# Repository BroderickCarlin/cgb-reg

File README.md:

# cgb-reg
CGB-REG chip replacement for Gameboy Color LCD drive circuitry

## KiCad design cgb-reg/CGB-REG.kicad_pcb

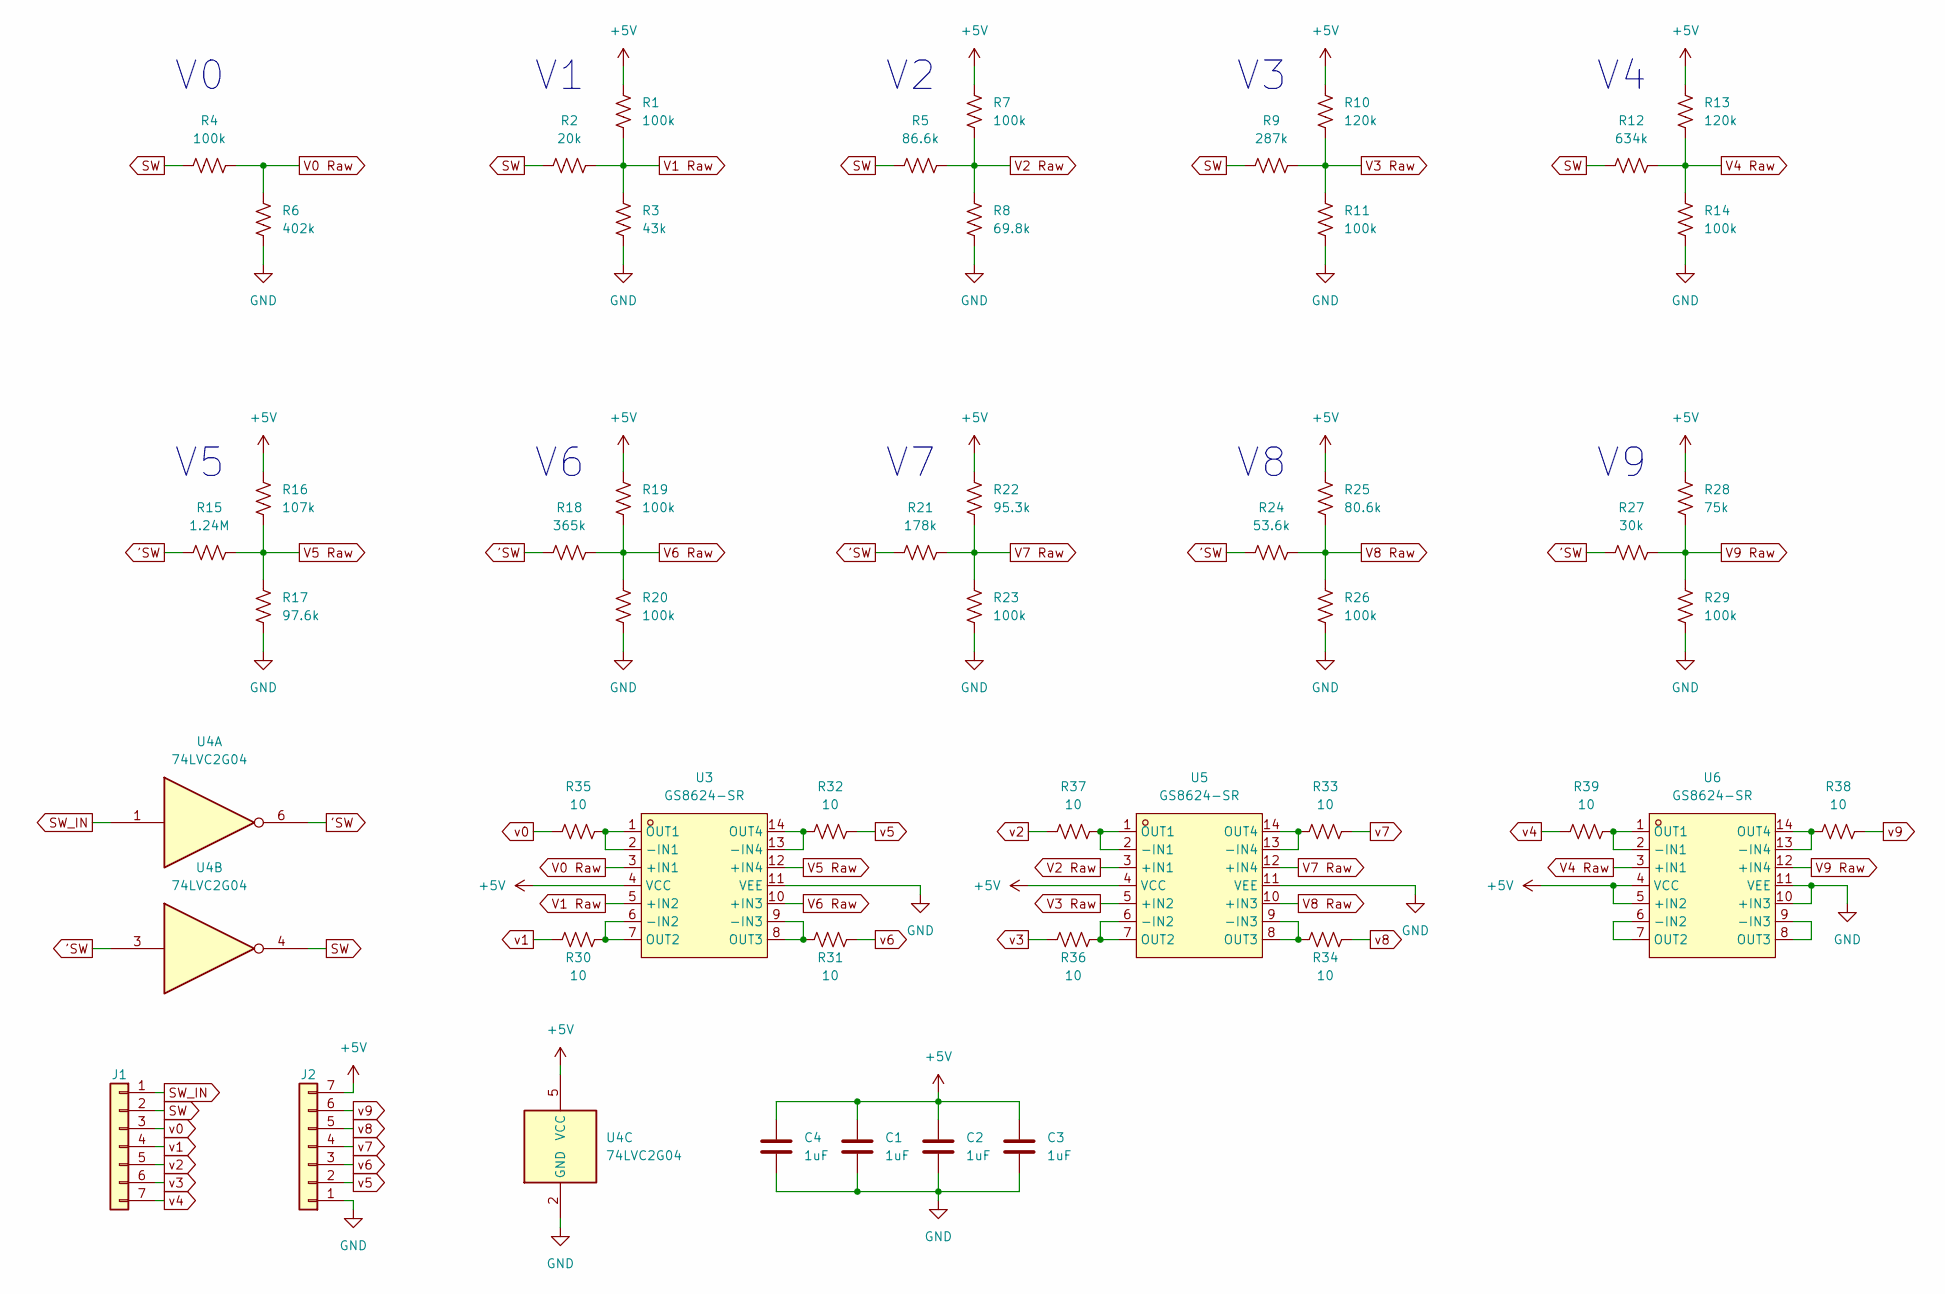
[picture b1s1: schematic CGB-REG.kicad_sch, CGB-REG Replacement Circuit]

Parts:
C1, C2, C3, C4: 1uF; C_0603_1608Metric; LCSC C89376
J1, J2: Conn_01x07; PinHeader_1x07_P2.54mm_Vertical
R1, R4, R7, R11, R14, R19, R20, R23, R26, R29: 100k; R_0603_1608Metric; LCSC C414506
R2: 20k; R_0603_1608Metric; LCSC C844340
R3: 43k; R_0603_1608Metric; LCSC C340523
R5: 86.6k; R_0603_1608Metric; LCSC C403381
R6: 402k; R_0603_1608Metric; LCSC C23048
R8: 69.8k; R_0603_1608Metric; LCSC C170663
R9: 287k; R_0603_1608Metric; LCSC C13174
R10, R13: 120k; R_0603_1608Metric; LCSC C325641
R12: 634k; R_0603_1608Metric; LCSC C321970
R15: 1.24M; R_0603_1608Metric; LCSC C367719
R16: 107k; R_0603_1608Metric; LCSC C103221
R17: 97.6k; R_0603_1608Metric; LCSC C507495
R18: 365k; R_0603_1608Metric; LCSC C367800
R21: 178k; R_0603_1608Metric; LCSC C103349
R22: 95.3k; R_0603_1608Metric; LCSC C912224
R24: 53.6k; R_0603_1608Metric; LCSC C103706
R25: 80.6k; R_0603_1608Metric; LCSC C2933260
R27: 30k; R_0603_1608Metric; LCSC C667692
R28: 75k; R_0603_1608Metric; LCSC C881187
R30, R31, R32, R33, R34, R35, R36, R37, R38, R39: 10; R_0603_1608Metric; LCSC C2791798
U3, U5, U6: GS8624-SR; SOIC-14_L8.6-W3.9-P1.27-LS6.0-BL; LCSC Part C605417
U4: 74LVC2G04; SOT-363_SC-70-6; LCSC C460538

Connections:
'SW: R15.2, R18.2, R21.2, R24.2, R27.2, U4.3, U4.6
+5V: C1.1, C2.1, C3.1, C4.1, J2.7, R1.1, R7.1, R10.1, R13.1, R16.1, R19.1, R22.1, R25.1, R28.1, U3.4 (VCC), U4.5 (VCC), U5.4 (VCC), U6.4 (VCC), U6.5 (+IN2)
GND: C1.2, C2.2, C3.2, C4.2, J2.1, R3.2, R6.2, R8.2, R11.2, R14.2, R17.2, R20.2, R23.2, R26.2, R29.2, U3.11 (VEE), U4.2 (GND), U5.11 (VEE), U6.10 (+IN3), U6.11 (VEE)
unnamed: R35.2, U3.1 (OUT1), U3.2 (-IN1)
unnamed: R30.2, U3.6 (-IN2), U3.7 (OUT2)
unnamed: R31.1, U3.8 (OUT3), U3.9 (-IN3)
unnamed: R32.1, U3.13 (-IN4), U3.14 (OUT4)
unnamed: R37.2, U5.1 (OUT1), U5.2 (-IN1)
unnamed: R36.2, U5.6 (-IN2), U5.7 (OUT2)
unnamed: R34.1, U5.8 (OUT3), U5.9 (-IN3)
unnamed: R33.1, U5.13 (-IN4), U5.14 (OUT4)
unnamed: R39.2, U6.1 (OUT1), U6.2 (-IN1)
unnamed: U6.6 (-IN2), U6.7 (OUT2)
unnamed: U6.8 (OUT3), U6.9 (-IN3)
unnamed: R38.2, U6.13 (-IN4), U6.14 (OUT4)
SW: J1.2, R2.2, R4.2, R5.2, R9.2, R12.2, U4.4
SW_IN: J1.1, U4.1
V0 Raw: R4.1, R6.1, U3.3 (+IN1)
V1 Raw: R1.2, R2.1, R3.1, U3.5 (+IN2)
V2 Raw: R5.1, R7.2, R8.1, U5.3 (+IN1)
V3 Raw: R9.1, R10.2, R11.1, U5.5 (+IN2)
V4 Raw: R12.1, R13.2, R14.1, U6.3 (+IN1)
V5 Raw: R15.1, R16.2, R17.1, U3.12 (+IN4)
V6 Raw: R18.1, R19.2, R20.1, U3.10 (+IN3)
V7 Raw: R21.1, R22.2, R23.1, U5.12 (+IN4)
V8 Raw: R24.1, R25.2, R26.1, U5.10 (+IN3)
V9 Raw: R27.1, R28.2, R29.1, U6.12 (+IN4)
v0: J1.3, R35.1
v1: J1.4, R30.1
v2: J1.5, R37.1
v3: J1.6, R36.1
v4: J1.7, R39.1
v5: J2.2, R32.2
v6: J2.3, R31.2
v7: J2.4, R33.2
v8: J2.5, R34.2
v9: J2.6, R38.1

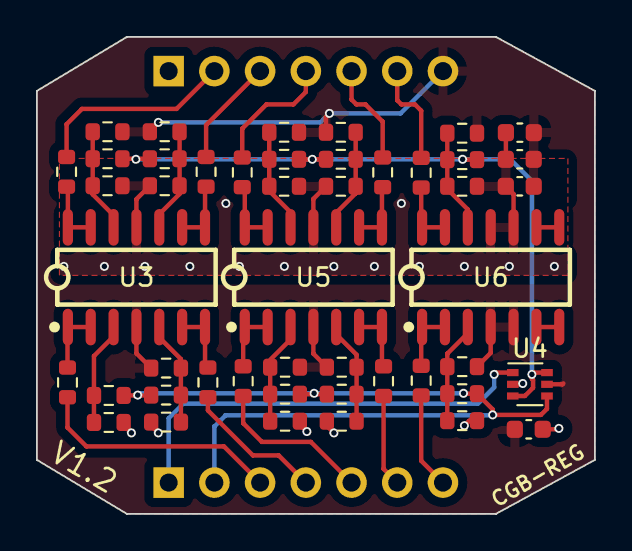
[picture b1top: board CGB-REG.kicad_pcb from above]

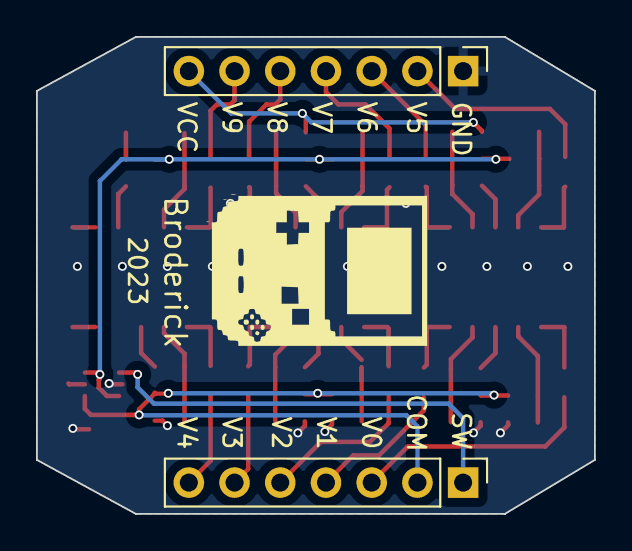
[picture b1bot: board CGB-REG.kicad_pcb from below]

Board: 2 copper layers, 31.0 x 26.5 mm, 49 parts (2 on the bottom side), 37 nets.

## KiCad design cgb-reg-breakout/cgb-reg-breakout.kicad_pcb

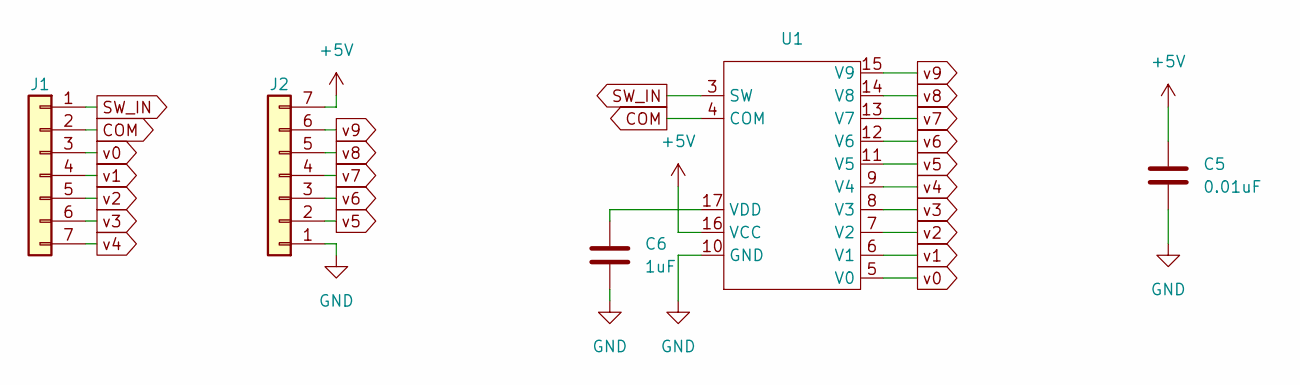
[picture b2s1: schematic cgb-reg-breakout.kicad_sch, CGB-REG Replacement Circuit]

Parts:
C5: 0.01uF; C_0603_1608Metric
C6: 1uF; C_0603_1608Metric; LCSC C89376
J1, J2: Conn_01x07; PinHeader_1x07_P2.54mm_Vertical
U1: CGB-REG

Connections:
+5V: C5.1, J2.7, U1.16 (VCC)
COM: J1.2, U1.4 (COM)
GND: C5.2, C6.2, J2.1, U1.10 (GND)
unnamed: C6.1, U1.17 (VDD)
SW_IN: J1.1, U1.3 (SW)
v0: J1.3, U1.5 (V0)
v1: J1.4, U1.6 (V1)
v2: J1.5, U1.7 (V2)
v3: J1.6, U1.8 (V3)
v4: J1.7, U1.9 (V4)
v5: J2.2, U1.11 (V5)
v6: J2.3, U1.12 (V6)
v7: J2.4, U1.13 (V7)
v8: J2.5, U1.14 (V8)
v9: J2.6, U1.15 (V9)

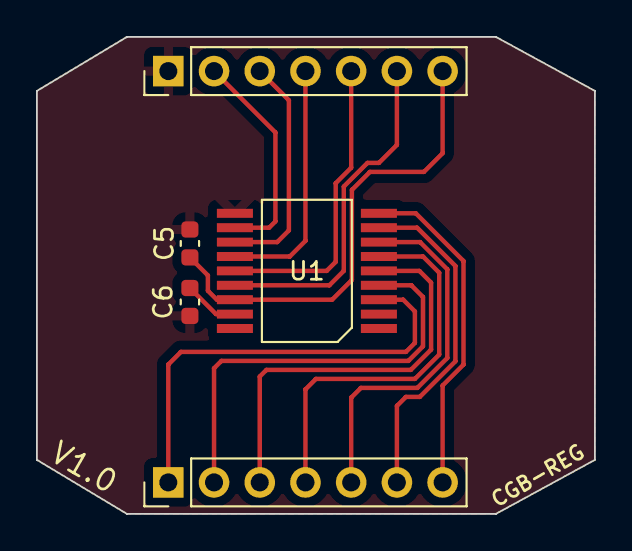
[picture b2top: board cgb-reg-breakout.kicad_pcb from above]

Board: 2 copper layers, 31.0 x 26.5 mm, 5 parts (0 on the bottom side), 15 nets.

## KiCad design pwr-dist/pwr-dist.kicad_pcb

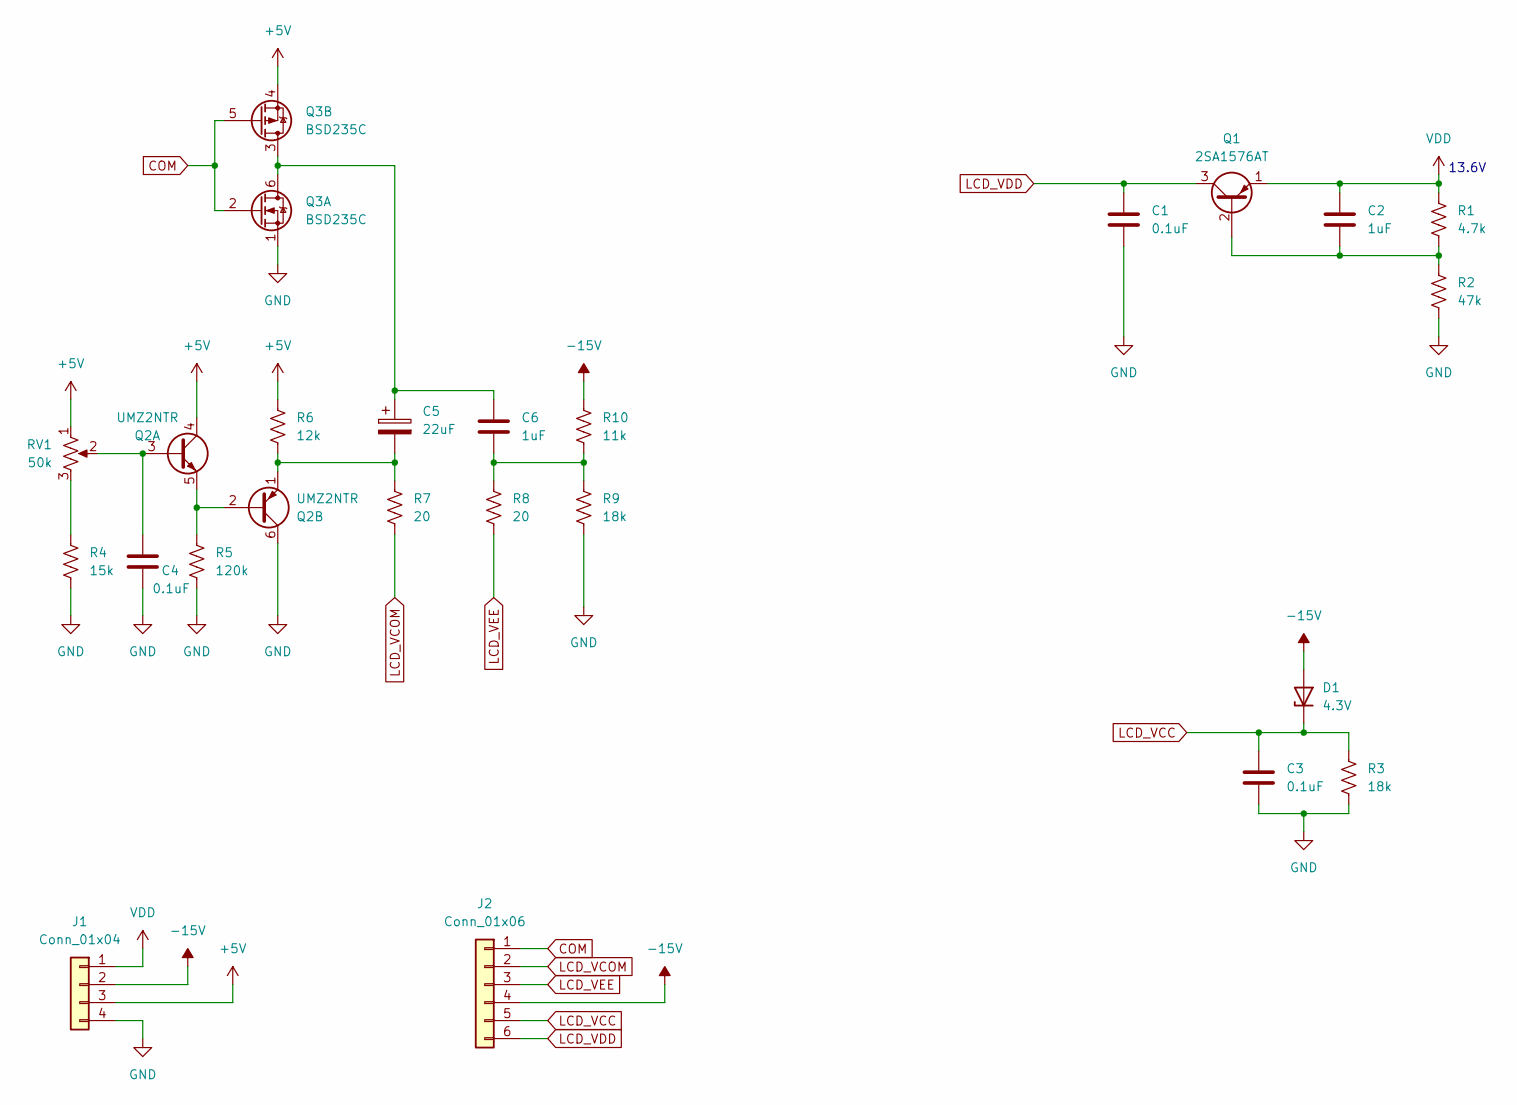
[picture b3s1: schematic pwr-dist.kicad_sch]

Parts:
C1, C3, C4: 0.1uF; R_0805_2012Metric_Pad1.20x1.40mm_HandSolder
C2, C6: 1uF; R_0805_2012Metric_Pad1.20x1.40mm_HandSolder
C5: 22uF; CP_Elec_4x5.3
D1: 4.3V; D_SOD-123
J1: Conn_01x04; PinHeader_1x04_P2.54mm_Vertical
J2: Conn_01x06; PinHeader_1x06_P2.54mm_Vertical
Q1: 2SA1576AT; SOT-323_SC-70_Handsoldering
Q2: UMZ2NTR; SOT-363_SC-70-6
Q3: BSD235C; SOT-666
R1: 4.7k; R_0805_2012Metric_Pad1.20x1.40mm_HandSolder
R2: 47k; R_0805_2012Metric_Pad1.20x1.40mm_HandSolder
R3, R9: 18k; R_0805_2012Metric_Pad1.20x1.40mm_HandSolder
R4: 15k; R_0805_2012Metric_Pad1.20x1.40mm_HandSolder
R5: 120k; R_0805_2012Metric_Pad1.20x1.40mm_HandSolder
R6: 12k; R_0805_2012Metric_Pad1.20x1.40mm_HandSolder
R7, R8: 20; R_0805_2012Metric_Pad1.20x1.40mm_HandSolder
R10: 11k; R_0805_2012Metric_Pad1.20x1.40mm_HandSolder
RV1: 50k; Potentiometer_Bourns_3314J_Vertical

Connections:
+5V: J1.3, Q2.4 (C1), Q3.4 (SP), R6.1, RV1.1
-15V: D1.2 (A), J1.2, J2.4, R10.1
COM: J2.1, Q3.2 (GN), Q3.5 (GP)
GND: C1.2, C3.2, C4.2, J1.4, Q2.6 (C2), Q3.1 (SN), R2.2, R3.2, R4.2, R5.2, R9.2
LCD_VCC: C3.1, D1.1 (K), J2.5, R3.1
LCD_VCOM: J2.2, R7.2
LCD_VDD: C1.1, J2.6, Q1.3 (C)
LCD_VEE: J2.3, R8.2
unnamed: C6.2, R8.1, R9.1, R10.2
unnamed: C2.2, Q1.2 (B), R1.2, R2.1
unnamed: C4.1, Q2.3 (B1), RV1.2
unnamed: Q2.2 (B2), Q2.5 (E1), R5.1
unnamed: C5.2, Q2.1 (E2), R6.2, R7.1
unnamed: C5.1, C6.1, Q3.3 (DP), Q3.6 (DN)
unnamed: R4.1, RV1.3
VDD: C2.1, J1.1, Q1.1 (E), R1.1

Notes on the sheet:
13.6V

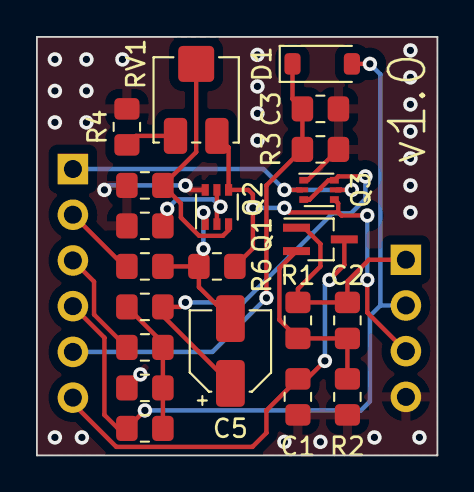
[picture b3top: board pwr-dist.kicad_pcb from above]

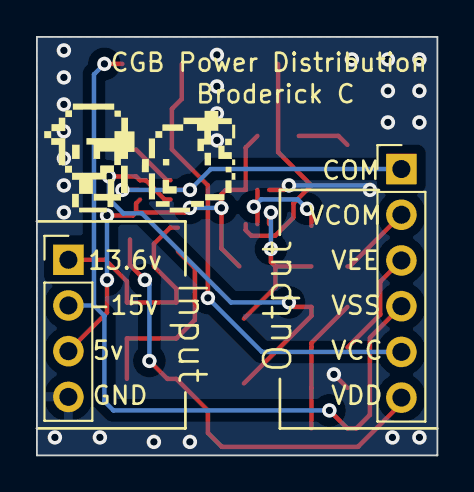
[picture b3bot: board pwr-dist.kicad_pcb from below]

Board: 2 copper layers, 22.2 x 23.2 mm, 23 parts (2 on the bottom side), 16 nets.

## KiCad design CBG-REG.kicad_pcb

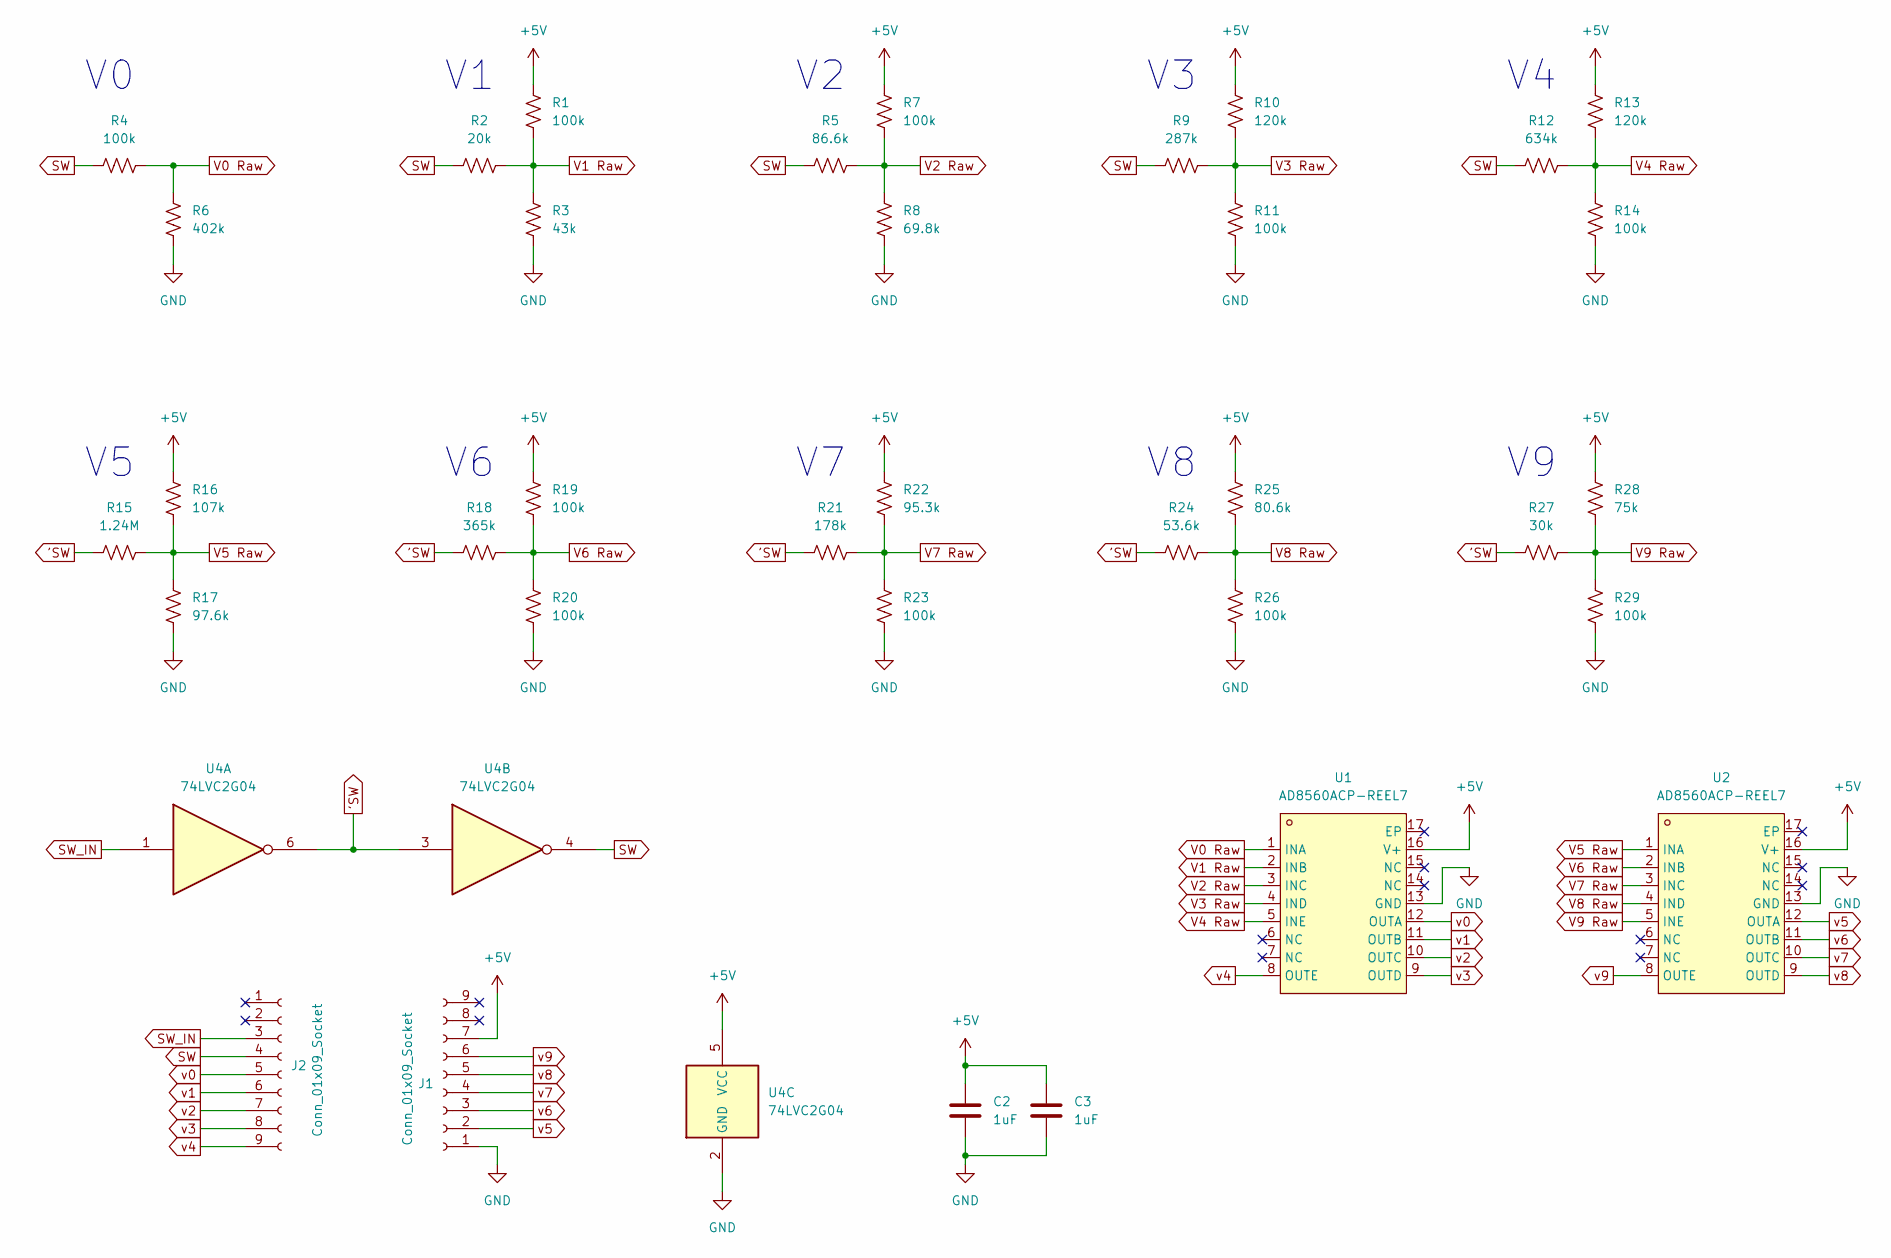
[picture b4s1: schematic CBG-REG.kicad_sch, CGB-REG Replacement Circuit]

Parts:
C2, C3: 1uF; C_0603_1608Metric; LCSC C89376
J1, J2: Conn_01x09_Socket; PinHeader_1x09_P2.00mm_Vertical
R1, R4, R7, R11, R14, R19, R20, R23, R26, R29: 100k; R_0603_1608Metric; LCSC C414506
R2: 20k; R_0603_1608Metric; LCSC C844340
R3: 43k; R_0603_1608Metric; LCSC C340523
R5: 86.6k; R_0603_1608Metric; LCSC C403381
R6: 402k; R_0603_1608Metric; LCSC C23048
R8: 69.8k; R_0603_1608Metric; LCSC C170663
R9: 287k; R_0603_1608Metric; LCSC C13174
R10, R13: 120k; R_0603_1608Metric; LCSC C325641
R12: 634k; R_0603_1608Metric; LCSC C321970
R15: 1.24M; R_0603_1608Metric; LCSC C367719
R16: 107k; R_0603_1608Metric; LCSC C103221
R17: 97.6k; R_0603_1608Metric; LCSC C507495
R18: 365k; R_0603_1608Metric; LCSC C367800
R21: 178k; R_0603_1608Metric; LCSC C103349
R22: 95.3k; R_0603_1608Metric; LCSC C912224
R24: 53.6k; R_0603_1608Metric; LCSC C103706
R25: 80.6k; R_0603_1608Metric; LCSC C2933260
R27: 30k; R_0603_1608Metric; LCSC C667692
R28: 75k; R_0603_1608Metric; LCSC C881187
U1, U2: AD8560ACP-REEL7; LFCSP-16_L4.0-W4.0-P0.65-TL-EP2.2; LCSC Part C4366758
U4: 74LVC2G04; SOT-23-6; LCSC C460538

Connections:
'SW: R15.2, R18.2, R21.2, R24.2, R27.2, U4.3, U4.6
+5V: C2.1, C3.1, J1.7, R1.1, R7.1, R10.1, R13.1, R16.1, R19.1, R22.1, R25.1, R28.1, U1.16 (V+), U2.16 (V+), U4.5 (VCC)
GND: C2.2, C3.2, J1.1, R3.2, R6.2, R8.2, R11.2, R14.2, R17.2, R20.2, R23.2, R26.2, R29.2, U1.13 (GND), U2.13 (GND), U4.2 (GND)
SW: J2.4, R2.2, R4.2, R5.2, R9.2, R12.2, U4.4
SW_IN: J2.3, U4.1
V0 Raw: R4.1, R6.1, U1.1 (INA)
V1 Raw: R1.2, R2.1, R3.1, U1.2 (INB)
V2 Raw: R5.1, R7.2, R8.1, U1.3 (INC)
V3 Raw: R9.1, R10.2, R11.1, U1.4 (IND)
V4 Raw: R12.1, R13.2, R14.1, U1.5 (INE)
V5 Raw: R15.1, R16.2, R17.1, U2.1 (INA)
V6 Raw: R18.1, R19.2, R20.1, U2.2 (INB)
V7 Raw: R21.1, R22.2, R23.1, U2.3 (INC)
V8 Raw: R24.1, R25.2, R26.1, U2.4 (IND)
V9 Raw: R27.1, R28.2, R29.1, U2.5 (INE)
v0: J2.5, U1.12 (OUTA)
v1: J2.6, U1.11 (OUTB)
v2: J2.7, U1.10 (OUTC)
v3: J2.8, U1.9 (OUTD)
v4: J2.9, U1.8 (OUTE)
v5: J1.2, U2.12 (OUTA)
v6: J1.3, U2.11 (OUTB)
v7: J1.4, U2.10 (OUTC)
v8: J1.5, U2.9 (OUTD)
v9: J1.6, U2.8 (OUTE)

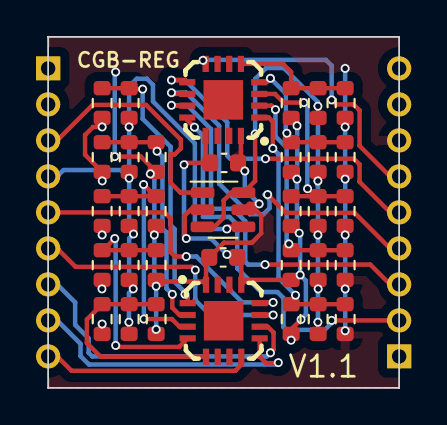
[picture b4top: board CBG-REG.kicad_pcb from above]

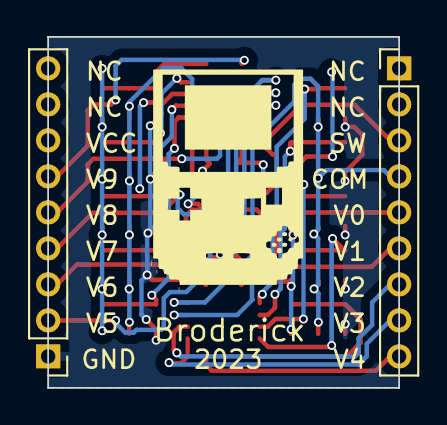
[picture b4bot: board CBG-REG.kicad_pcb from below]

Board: 2 copper layers, 19.5 x 19.5 mm, 36 parts (2 on the bottom side), 25 nets.

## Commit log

2023-10-23 feat: Initial commit
2023-10-24 fix: Update resistor values to those in stock at JLCPCB
2023-10-24 feat: Add PCB silkscreen
2023-10-25 feat: Update accuracy of V5 signal
2023-10-25 docs: Add pinout to the silkscreen
2023-10-25 feat: Switch connector to use castellations
2023-10-25 feat: Add Task file for generating gerbers
2023-10-25 feat(Task): Make failures to build the temp dir an actual failure
2023-10-25 fix(Task): Fix generating drill operation not using proper output dir
2023-10-30 feat: Bump schematic version to v1.1
2023-11-02 feat: Redesign the board to use an IC that JLCPCB has in stock
2023-11-13 feat: Add v1.0 of power distribution board
    also slight reorg of repo
2023-11-14 feat: Add a new breakout for the official CGB-REG IC
2023-11-17 fix: Fix wrong footprint for inverter IC
